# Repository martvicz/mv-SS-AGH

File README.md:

# Greetings!
Here is my work for the second phase of admissions to the AGH Space Systems. I only completed 2 tasks, but I hope it is enough!
The answers to the tasks were uploaded as 2 separate directories:

# Task_1.1
Contains answers relating to the AP63300 converter module task, including the KiCad project files, the report, and the images used in the report.

# Task_2.1
Contains answers relating to the LED Blinker task (the entire STM32 CMake project)

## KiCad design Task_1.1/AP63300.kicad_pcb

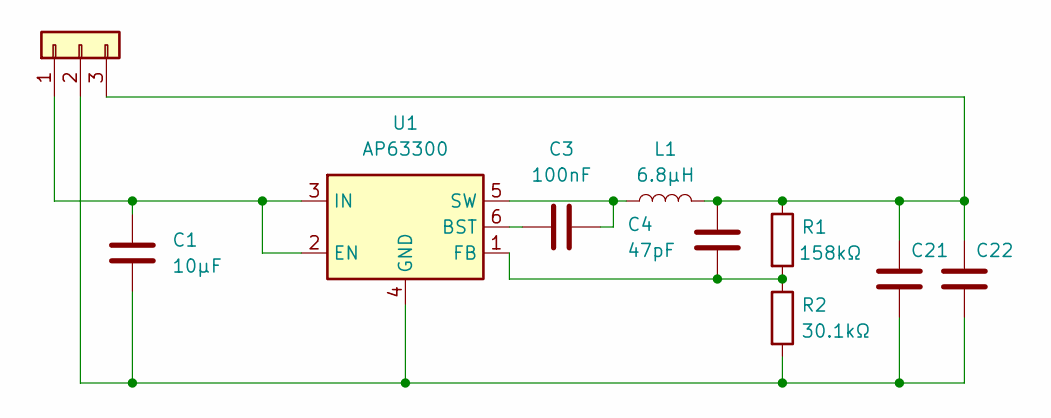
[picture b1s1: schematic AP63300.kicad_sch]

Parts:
C1: 10μF; C_1210_3225Metric; MPN AGC1210X7R500-106KNE
C3: 100nF; C_0603_1608Metric; MPN CC0603KRX7R7BB104
C4: 47pF; C_0603_1608Metric; MPN 885012006021
C21, C22: 22μF; C_1210_3225Metric; MPN FTC1210X7R250-226KNE
J1: Conn_01x03; PinHeader_1x03_P2.54mm_Vertical; MPN PH1-03-UA
L1: 6.8μH; L_Wurth_WE-PD2A-7850; MPN 784775068
R1: 158kΩ; R_0603_1608Metric; MPN RC0603FR-07158KL
R2: 30.1kΩ; R_0603_1608Metric; MPN RK73H1JTTD3012F
U1: AP63300; TSOT-23-6; MPN AP63300WU-7

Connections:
BST: C3.1, U1.6 (BST)
FB: C4.2, R1.2, R2.1, U1.1 (FB)
GND: C1.2, C21.2, C22.2, J1.2, R2.2, U1.4 (GND)
SW: C3.2, L1.1, U1.5 (SW)
VIN: C1.1, J1.1, U1.2 (EN), U1.3 (IN)
VOUT: C4.1, C21.1, C22.1, J1.3, L1.2, R1.1

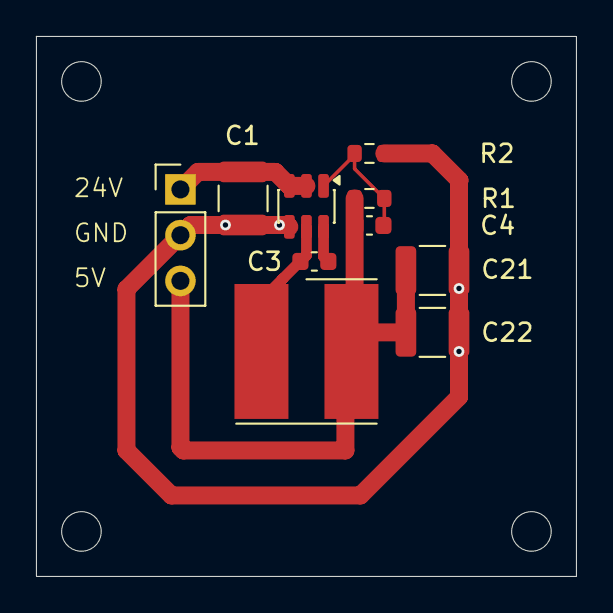
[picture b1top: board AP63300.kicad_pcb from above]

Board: 2 copper layers, 30.0 x 30.0 mm, 10 parts (0 on the bottom side), 6 nets.
